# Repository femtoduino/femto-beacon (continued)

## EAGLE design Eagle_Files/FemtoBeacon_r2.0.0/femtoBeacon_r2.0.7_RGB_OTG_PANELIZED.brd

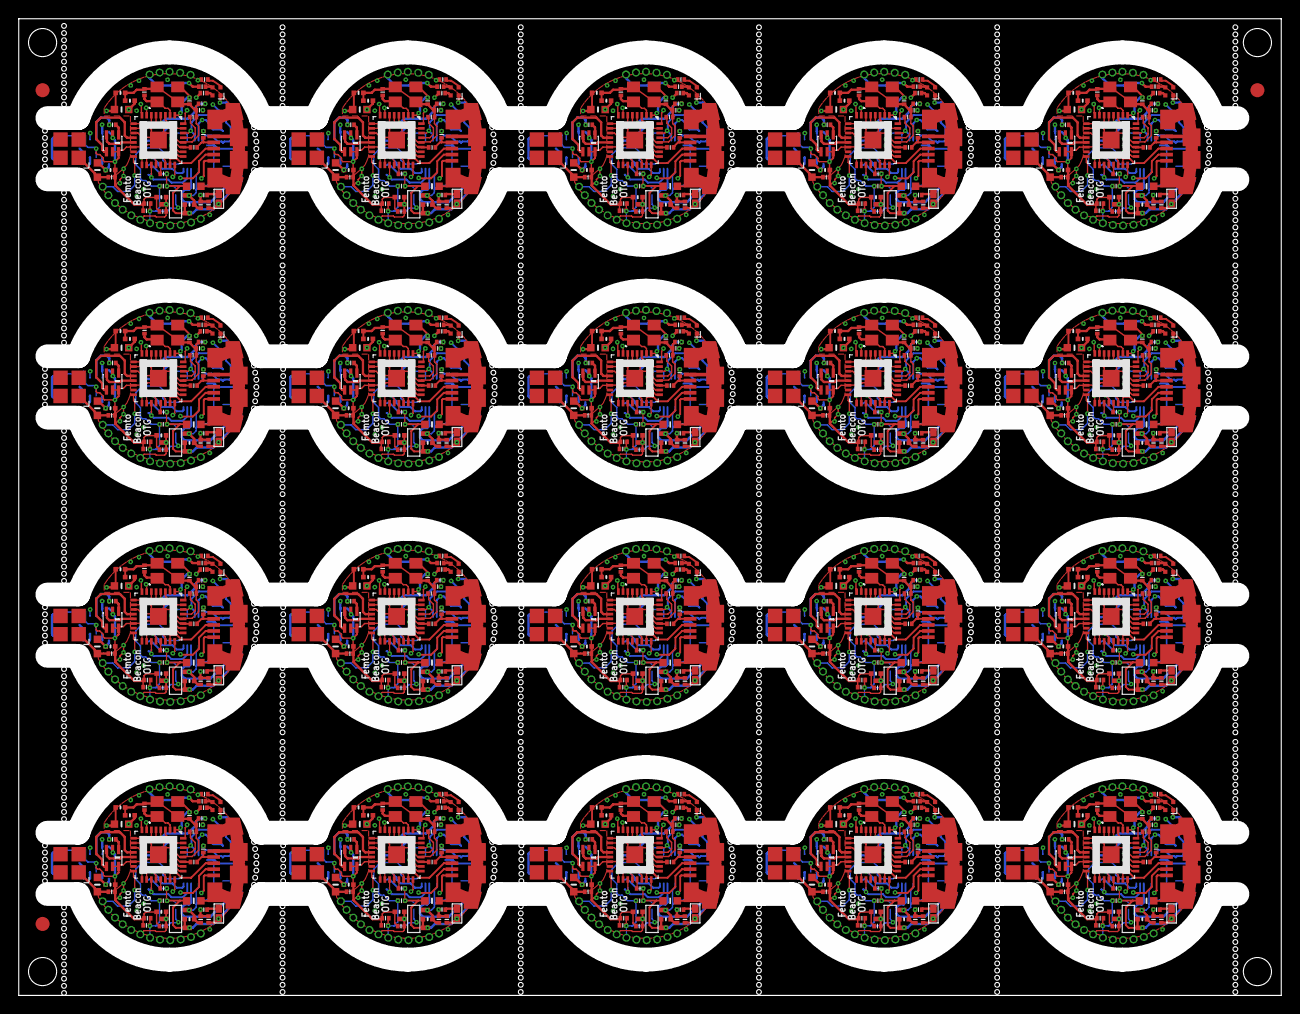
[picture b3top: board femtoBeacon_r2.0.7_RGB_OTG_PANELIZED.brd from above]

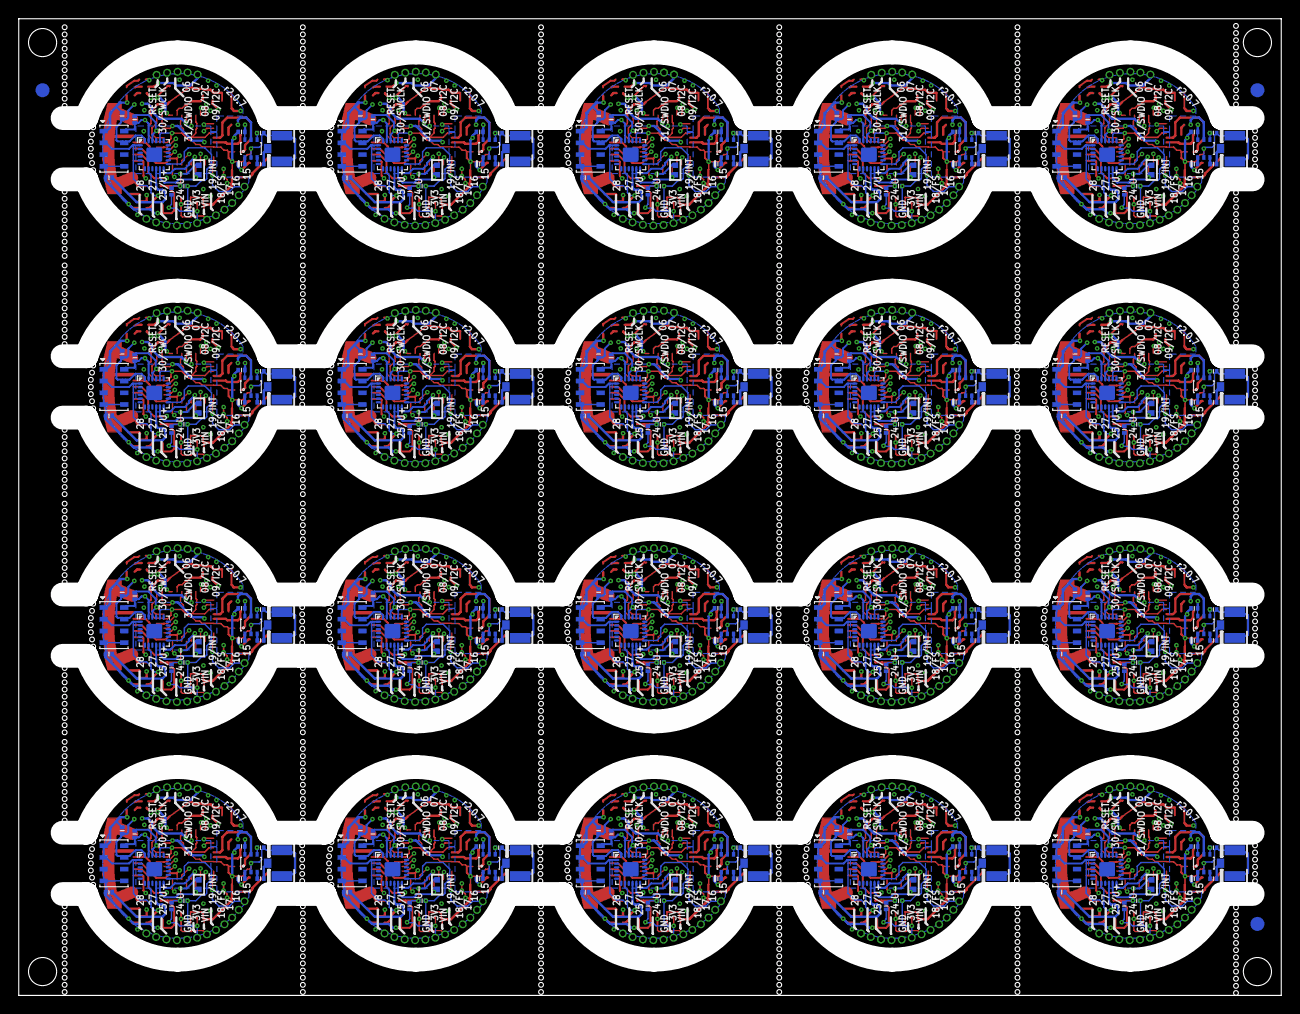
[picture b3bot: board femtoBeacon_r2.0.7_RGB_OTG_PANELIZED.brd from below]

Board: 4 copper layers, 134.6 x 104.1 mm, 1346 parts (283 on the bottom side), 820 nets.

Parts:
ANT_SMD, ANT_SMD1, ANT_SMD2, ANT_SMD3, ANT_SMD4, ANT_SMD5, ANT_SMD6, ANT_SMD7, ANT_SMD8, ANT_SMD9, ANT_SMD10, ANT_SMD11, ANT_SMD12, ANT_SMD13, ANT_SMD14, ANT_SMD15, ANT_SMD16, ANT_SMD17, ANT_SMD18, ANT_SMD19: 0479480001
ASWITCH, ASWITCH1, ASWITCH2, ASWITCH3, ASWITCH4, ASWITCH5, ASWITCH6, ASWITCH7, ASWITCH8, ASWITCH9, ASWITCH10, ASWITCH11, ASWITCH12, ASWITCH13, ASWITCH14, ASWITCH15, ASWITCH16, ASWITCH17, ASWITCH18, ASWITCH19: AS222-92LF
BALUN, BALUN1, BALUN2, BALUN3, BALUN4, BALUN5, BALUN6, BALUN7, BALUN8, BALUN9, BALUN10, BALUN11, BALUN12, BALUN13, BALUN14, BALUN15, BALUN16, BALUN17, BALUN18, BALUN19: JOHANSON_2450BM15A0015E; 0805_BALUN
BARO, BARO1, BARO2, BARO3, BARO4, BARO5, BARO6, BARO7, BARO8, BARO9, BARO10, BARO11, BARO12, BARO13, BARO14, BARO15, BARO16, BARO17, BARO18, BARO19: MS5611-01BA03
BTN, BTN1, BTN2, BTN3, BTN4, BTN5, BTN6, BTN7, BTN8, BTN9, BTN10, BTN11, BTN12, BTN13, BTN14, BTN15, BTN16, BTN17, BTN18, BTN19: DNP; SPST_SMD
C1, C2, C3, C4, C8, C9, C10, C16, C17, C27, C28, C29, C30, C32, C33, C34, C35, C38, C42, C43, C51, C52, C56, C57, C58, C59, C60, C63, C67, C68, C76, C77, C81, C82, C83, C84, C85, C88, C92, C93, C101, C102, C106, C107, C108, C109, C110, C113, C117, C118, C126, C127, C131, C132, C133, C134, C135, C138, C142, C143, C151, C152, C156, C157, C158, C159, C160, C163, C167, C168, C176, C177, C181, C182, C183, C184, C185, C188, C192, C193, C201, C202, C206, C207, C208, C209, C210, C213, C217, C218, C226, C227, C231, C232, C233, C234, C235, C238, C242, C243, C251, C252, C256, C257, C258, C259, C260, C263, C267, C268, C276, C277, C281, C282, C283, C284, C285, C288, C292, C293, C301, C302, C306, C307, C308, C309, C310, C313, C317, C318, C326, C327, C331, C332, C333, C334, C335, C338, C342, C343, C351, C352, C356, C357, C358, C359, C360, C363, C367, C368, C376, C377, C381, C382, C383, C384, C385, C388, C392, C393, C401, C402, C406, C407, C408, C409, C410, C413, C417, C418, C426, C427, C431, C432, C433, C434, C435, C438, C442, C443, C451, C452, C456, C457, C458, C459, C460, C463, C467, C468, C476, C477, C481, C482, C483, C484, C485, C488, C492, C493: 0.1uF; PART
C5, C6, C24, C25, C53, C54, C78, C79, C103, C104, C128, C129, C153, C154, C178, C179, C203, C204, C228, C229, C253, C254, C278, C279, C303, C304, C328, C329, C353, C354, C378, C379, C403, C404, C428, C429, C453, C454, C478, C479: 2.2uF; _0402MP
C7, C26, C55, C80, C105, C130, C155, C180, C205, C230, C255, C280, C305, C330, C355, C380, C405, C430, C455, C480: 0.47uF; PART
C11, C45, C70, C95, C120, C145, C170, C195, C220, C245, C270, C295, C320, C345, C370, C395, C420, C445, C470, C495: 1.2pF; _0402MP
C12, C18, C19, C20, C23, C46, C47, C48, C49, C50, C71, C72, C73, C74, C75, C96, C97, C98, C99, C100, C121, C122, C123, C124, C125, C146, C147, C148, C149, C150, C171, C172, C173, C174, C175, C196, C197, C198, C199, C200, C221, C222, C223, C224, C225, C246, C247, C248, C249, C250, C271, C272, C273, C274, C275, C296, C297, C298, C299, C300, C321, C322, C323, C324, C325, C346, C347, C348, C349, C350, C371, C372, C373, C374, C375, C396, C397, C398, C399, C400, C421, C422, C423, C424, C425, C446, C447, C448, C449, C450, C471, C472, C473, C474, C475, C496, C497, C498, C499, C500: 22pF; PART
C13, C44, C69, C94, C119, C144, C169, C194, C219, C244, C269, C294, C319, C344, C369, C394, C419, C444, C469, C494: DNP; PART
C14, C15, C39, C40, C64, C65, C89, C90, C114, C115, C139, C140, C164, C165, C189, C190, C214, C215, C239, C240, C264, C265, C289, C290, C314, C315, C339, C340, C364, C365, C389, C390, C414, C415, C439, C440, C464, C465, C489, C490: 9pF; PART
C21, C22, C36, C37, C61, C62, C86, C87, C111, C112, C136, C137, C161, C162, C186, C187, C211, C212, C236, C237, C261, C262, C286, C287, C311, C312, C336, C337, C361, C362, C386, C387, C411, C412, C436, C437, C461, C462, C486, C487: 10uF; _0402MP
C31, C41, C66, C91, C116, C141, C166, C191, C216, C241, C266, C291, C316, C341, C366, C391, C416, C441, C466, C491: 10nF; PART
FB1, FB2, FB3, FB4, FB5, FB6, FB7, FB8, FB9, FB10, FB11, FB12, FB13, FB14, FB15, FB16, FB17, FB18, FB19, FB20: Ferrite; _0603MP
FID1, FID2, FID3, FID4, FID5, FID6: FIDUCIAL; FIDUCIAL_1MM
IC, IC1, IC2, IC3, IC4, IC5, IC6, IC7, IC8, IC9, IC10, IC11, IC12, IC13, IC14, IC15, IC16, IC17, IC18, IC19: ATSAMR21E18A-MUT; QFN32
IMU, IMU1, IMU2, IMU3, IMU4, IMU5, IMU6, IMU7, IMU8, IMU9, IMU10, IMU11, IMU12, IMU13, IMU14, IMU15, IMU16, IMU17, IMU18, IMU19: MPU-9250; QFN_3X3MM
L1, L3, L5, L8, L10, L12, L14, L16, L18, L20, L22, L24, L26, L28, L30, L32, L34, L36, L38, L40: 1.8nH; _0603MP
L2, L4, L6, L7, L9, L11, L13, L15, L17, L19, L21, L23, L25, L27, L29, L31, L33, L35, L37, L39: 10uH; _0603MP
LDO_VREG, LDO_VREG1, LDO_VREG2, LDO_VREG3, LDO_VREG4, LDO_VREG5, LDO_VREG6, LDO_VREG7, LDO_VREG8, LDO_VREG9, LDO_VREG10, LDO_VREG11, LDO_VREG12, LDO_VREG13, LDO_VREG14, LDO_VREG15, LDO_VREG16, LDO_VREG17, LDO_VREG18, LDO_VREG19: MCP1700T-3302E/TT
R1, R4, R5, R6, R7, R11, R16, R17, R18, R19, R21, R26, R27, R28, R29, R31, R36, R37, R38, R39, R41, R46, R47, R48, R49, R51, R56, R57, R58, R59, R61, R66, R67, R68, R69, R71, R76, R77, R78, R79, R81, R86, R87, R88, R89, R91, R96, R97, R98, R99, R101, R106, R107, R108, R109, R111, R116, R117, R118, R119, R121, R126, R127, R128, R129, R131, R136, R137, R138, R139, R141, R146, R147, R148, R149, R151, R156, R157, R158, R159, R161, R166, R167, R168, R169, R171, R176, R177, R178, R179, R181, R186, R187, R188, R189, R191, R196, R197, R198, R199: 330; PART
R2, R12, R22, R32, R42, R52, R62, R72, R82, R92, R102, R112, R122, R132, R142, R152, R162, R172, R182, R192: 10K; PART
R3, R15, R25, R35, R45, R55, R65, R75, R85, R95, R105, R115, R125, R135, R145, R155, R165, R175, R185, R195: 330; _0402
R8, R9, R13, R14, R23, R24, R33, R34, R43, R44, R53, R54, R63, R64, R73, R74, R83, R84, R93, R94, R103, R104, R113, R114, R123, R124, R133, R134, R143, R144, R153, R154, R163, R164, R173, R174, R183, R184, R193, R194: 2.2K; PART
R10, R20, R30, R40, R50, R60, R70, R80, R90, R100, R110, R120, R130, R140, R150, R160, R170, R180, R190, R200: 100K; PART
RGBLED, RGBLED1, RGBLED2, RGBLED3, RGBLED4, RGBLED5, RGBLED6, RGBLED7, RGBLED8, RGBLED9, RGBLED10, RGBLED11, RGBLED12, RGBLED13, RGBLED14, RGBLED15, RGBLED16, RGBLED17, RGBLED18, RGBLED19: LRTB_R48G
U$1, U$2, U$3, U$4, U$5, U$6, U$7, U$8, U$9, U$10, U$11, U$12, U$13, U$14, U$15, U$16, U$17, U$18, U$19, U$20, U$21, U$22, U$23, U$24, U$25, U$26, U$27, U$28, U$29, U$30, U$31, U$32, U$33, U$34, U$35, U$36, U$37, U$38, U$39, U$40, U$41, U$42, U$43, U$44, U$45, U$46, U$47, U$48, U$49, U$50, U$51, U$52, U$53, U$54, U$55, U$56, U$57, U$58, U$59, U$60, U$61, U$62, U$63, U$64, U$65, U$66, U$67, U$68, U$69, U$70, U$71, U$72, U$73, U$74, U$75, U$76, U$77, U$78, U$79, U$80, U$81, U$82, U$83, U$84, U$85, U$86, U$87, U$88, U$89, U$90, U$91, U$92, U$93, U$94, U$95, U$96, U$97, U$98, U$99, U$100, U$101, U$102, U$103, U$104, U$105, U$106, U$107, U$108, U$109, U$110, U$111, U$112, U$113, U$114, U$115, U$116, U$117, U$118, U$119, U$120, U$121, U$122, U$123, U$124, U$125, U$126, U$127, U$128, U$129, U$130, U$131, U$132, U$133, U$134, U$135, U$136, U$137, U$138, U$139, U$140, U$141, U$142, U$143, U$144, U$145, U$146, U$147, U$148, U$149, U$150, U$151, U$152, U$153, U$154, U$155, U$156, U$157, U$158, U$159, U$160, U$161, U$162, U$163, U$164, U$165, U$166, U$167, U$168, U$169, U$170, U$171, U$172, U$173, U$174, U$175, U$176, U$177, U$178, U$179, U$180, U$181, U$182, U$183, U$184, U$185, U$186, U$187, U$188, U$189, U$190, U$191, U$192, U$193, U$194, U$195, U$196, U$197, U$198, U$199, U$200, U$201, U$202, U$203, U$204, U$205, U$206, U$207, U$208, U$209, U$210, U$211, U$212, U$213, U$214, U$215, U$216, U$217, U$218, U$219, U$220, U$221, U$222, U$223, U$224, U$225, U$226, U$227, U$228, U$229, U$230, U$231, U$232, U$233, U$234, U$235, U$236, U$237, U$238, U$239, U$240, U$241, U$242, U$243, U$244, U$245, U$246, U$247, U$248, U$249, U$250, U$251, U$252, U$253, U$254, U$255, U$256, U$257, U$258, U$259, U$260, U$261, U$262, U$263, U$264, U$265, U$266, U$267, U$268, U$269, U$270, U$271, U$272, U$273, U$274, U$275, U$276, U$277, U$278, U$279, U$280, U$281, U$282, U$283, U$284, U$285, U$286, U$287, U$288, U$289, U$290, U$291, U$292, U$293, U$294, U$295, U$296, U$297, U$298, U$299, U$300, U$301, U$302, U$303, U$304, U$305, U$306, U$307, U$308, U$309, U$310, U$311, U$312, U$313, U$314, U$315, U$316, U$317, U$318, U$319, U$320, U$321, U$322, U$323, U$324, U$325, U$326, U$327, U$328, U$329, U$330, U$331, U$332, U$333, U$334, U$335, U$336, U$337, U$338, U$339, U$340: 1X1_ROUND
UFLANT, UFLANT1, UFLANT2, UFLANT3, UFLANT4, UFLANT5, UFLANT6, UFLANT7, UFLANT8, UFLANT9, UFLANT10, UFLANT11, UFLANT12, UFLANT13, UFLANT14, UFLANT15, UFLANT16, UFLANT17, UFLANT18, UFLANT19: uFL; U.FL
USB, USB1, USB2, USB3, USB4, USB5, USB6, USB7, USB8, USB9, USB10, USB11, USB12, USB13, USB14, USB15, USB16, USB17, USB18, USB19: USB_MICROB; USB_MICROB_PACKAGE
XOSCRF, XOSCRF1, XOSCRF2, XOSCRF3, XOSCRF4, XOSCRF5, XOSCRF6, XOSCRF7, XOSCRF8, XOSCRF9, XOSCRF10, XOSCRF11, XOSCRF12, XOSCRF13, XOSCRF14, XOSCRF15, XOSCRF16, XOSCRF17, XOSCRF18, XOSCRF19: 16MHz; TSX-3225

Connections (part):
3.3V: BARO.1, BARO.2, C5.1, C10.1, C16.1, C21.2, C29.1, C30.2, C31.2, IC.24, IC.30, IMU.P$1, IMU.P$8, IMU.P$13, IMU.P$22, L6.1, LDO_VREG.VOUT, R2.2, R8.2, R9.2, R10.2, RGBLED.1, U$5.P$1
3.3V1: BARO1.1, BARO1.2, C24.1, C27.1, C34.1, C36.2, C38.1, C41.2, C42.2, IC1.24, IC1.30, IMU1.P$1, IMU1.P$8, IMU1.P$13, IMU1.P$22, L2.1, LDO_VREG1.VOUT, R12.2, R13.2, R14.2, R20.2, RGBLED1.1, U$6.P$1
3.3V2: BARO2.1, BARO2.2, C53.1, C56.1, C59.1, C61.2, C63.1, C66.2, C67.2, IC2.24, IC2.30, IMU2.P$1, IMU2.P$8, IMU2.P$13, IMU2.P$22, L4.1, LDO_VREG2.VOUT, R22.2, R23.2, R24.2, R30.2, RGBLED2.1, U$26.P$1
3.3V3: BARO3.1, BARO3.2, C78.1, C81.1, C84.1, C86.2, C88.1, C91.2, C92.2, IC3.24, IC3.30, IMU3.P$1, IMU3.P$8, IMU3.P$13, IMU3.P$22, L7.1, LDO_VREG3.VOUT, R32.2, R33.2, R34.2, R40.2, RGBLED3.1, U$53.P$1
3.3V4: BARO4.1, BARO4.2, C103.1, C106.1, C109.1, C111.2, C113.1, C116.2, C117.2, IC4.24, IC4.30, IMU4.P$1, IMU4.P$8, IMU4.P$13, IMU4.P$22, L9.1, LDO_VREG4.VOUT, R42.2, R43.2, R44.2, R50.2, RGBLED4.1, U$71.P$1
3.3V5: BARO5.1, BARO5.2, C128.1, C131.1, C134.1, C136.2, C138.1, C141.2, C142.2, IC5.24, IC5.30, IMU5.P$1, IMU5.P$8, IMU5.P$13, IMU5.P$22, L11.1, LDO_VREG5.VOUT, R52.2, R53.2, R54.2, R60.2, RGBLED5.1, U$88.P$1
3.3V6: BARO6.1, BARO6.2, C153.1, C156.1, C159.1, C161.2, C163.1, C166.2, C167.2, IC6.24, IC6.30, IMU6.P$1, IMU6.P$8, IMU6.P$13, IMU6.P$22, L13.1, LDO_VREG6.VOUT, R62.2, R63.2, R64.2, R70.2, RGBLED6.1, U$105.P$1
3.3V7: BARO7.1, BARO7.2, C178.1, C181.1, C184.1, C186.2, C188.1, C191.2, C192.2, IC7.24, IC7.30, IMU7.P$1, IMU7.P$8, IMU7.P$13, IMU7.P$22, L15.1, LDO_VREG7.VOUT, R72.2, R73.2, R74.2, R80.2, RGBLED7.1, U$122.P$1
3.3V8: BARO8.1, BARO8.2, C203.1, C206.1, C209.1, C211.2, C213.1, C216.2, C217.2, IC8.24, IC8.30, IMU8.P$1, IMU8.P$8, IMU8.P$13, IMU8.P$22, L17.1, LDO_VREG8.VOUT, R82.2, R83.2, R84.2, R90.2, RGBLED8.1, U$139.P$1
3.3V9: BARO9.1, BARO9.2, C228.1, C231.1, C234.1, C236.2, C238.1, C241.2, C242.2, IC9.24, IC9.30, IMU9.P$1, IMU9.P$8, IMU9.P$13, IMU9.P$22, L19.1, LDO_VREG9.VOUT, R92.2, R93.2, R94.2, R100.2, RGBLED9.1, U$156.P$1
3.3V10: BARO10.1, BARO10.2, C253.1, C256.1, C259.1, C261.2, C263.1, C266.2, C267.2, IC10.24, IC10.30, IMU10.P$1, IMU10.P$8, IMU10.P$13, IMU10.P$22, L21.1, LDO_VREG10.VOUT, R102.2, R103.2, R104.2, R110.2, RGBLED10.1, U$173.P$1
3.3V11: BARO11.1, BARO11.2, C278.1, C281.1, C284.1, C286.2, C288.1, C291.2, C292.2, IC11.24, IC11.30, IMU11.P$1, IMU11.P$8, IMU11.P$13, IMU11.P$22, L23.1, LDO_VREG11.VOUT, R112.2, R113.2, R114.2, R120.2, RGBLED11.1, U$190.P$1
3.3V12: BARO12.1, BARO12.2, C303.1, C306.1, C309.1, C311.2, C313.1, C316.2, C317.2, IC12.24, IC12.30, IMU12.P$1, IMU12.P$8, IMU12.P$13, IMU12.P$22, L25.1, LDO_VREG12.VOUT, R122.2, R123.2, R124.2, R130.2, RGBLED12.1, U$207.P$1
3.3V13: BARO13.1, BARO13.2, C328.1, C331.1, C334.1, C336.2, C338.1, C341.2, C342.2, IC13.24, IC13.30, IMU13.P$1, IMU13.P$8, IMU13.P$13, IMU13.P$22, L27.1, LDO_VREG13.VOUT, R132.2, R133.2, R134.2, R140.2, RGBLED13.1, U$224.P$1
3.3V14: BARO14.1, BARO14.2, C353.1, C356.1, C359.1, C361.2, C363.1, C366.2, C367.2, IC14.24, IC14.30, IMU14.P$1, IMU14.P$8, IMU14.P$13, IMU14.P$22, L29.1, LDO_VREG14.VOUT, R142.2, R143.2, R144.2, R150.2, RGBLED14.1, U$241.P$1
3.3V15: BARO15.1, BARO15.2, C378.1, C381.1, C384.1, C386.2, C388.1, C391.2, C392.2, IC15.24, IC15.30, IMU15.P$1, IMU15.P$8, IMU15.P$13, IMU15.P$22, L31.1, LDO_VREG15.VOUT, R152.2, R153.2, R154.2, R160.2, RGBLED15.1, U$258.P$1
3.3V16: BARO16.1, BARO16.2, C403.1, C406.1, C409.1, C411.2, C413.1, C416.2, C417.2, IC16.24, IC16.30, IMU16.P$1, IMU16.P$8, IMU16.P$13, IMU16.P$22, L33.1, LDO_VREG16.VOUT, R162.2, R163.2, R164.2, R170.2, RGBLED16.1, U$275.P$1
3.3V17: BARO17.1, BARO17.2, C428.1, C431.1, C434.1, C436.2, C438.1, C441.2, C442.2, IC17.24, IC17.30, IMU17.P$1, IMU17.P$8, IMU17.P$13, IMU17.P$22, L35.1, LDO_VREG17.VOUT, R172.2, R173.2, R174.2, R180.2, RGBLED17.1, U$292.P$1
3.3V18: BARO18.1, BARO18.2, C453.1, C456.1, C459.1, C461.2, C463.1, C466.2, C467.2, IC18.24, IC18.30, IMU18.P$1, IMU18.P$8, IMU18.P$13, IMU18.P$22, L37.1, LDO_VREG18.VOUT, R182.2, R183.2, R184.2, R190.2, RGBLED18.1, U$309.P$1
3.3V19: BARO19.1, BARO19.2, C478.1, C481.1, C484.1, C486.2, C488.1, C491.2, C492.2, IC19.24, IC19.30, IMU19.P$1, IMU19.P$8, IMU19.P$13, IMU19.P$22, L39.1, LDO_VREG19.VOUT, R192.2, R193.2, R194.2, R200.2, RGBLED19.1, U$326.P$1
ANT_LINE: ANT_SMD.ANT, C13.1, L1.2
ANT_LINE1: ANT_SMD1.ANT, C44.1, L3.2
ANT_LINE2: ANT_SMD2.ANT, C69.1, L5.2
ANT_LINE3: ANT_SMD3.ANT, C94.1, L8.2
ANT_LINE4: ANT_SMD4.ANT, C119.1, L10.2
ANT_LINE5: ANT_SMD5.ANT, C144.1, L12.2
ANT_LINE6: ANT_SMD6.ANT, C169.1, L14.2
ANT_LINE7: ANT_SMD7.ANT, C194.1, L16.2
ANT_LINE8: ANT_SMD8.ANT, C219.1, L18.2
ANT_LINE9: ANT_SMD9.ANT, C244.1, L20.2
ANT_LINE10: ANT_SMD10.ANT, C269.1, L22.2
ANT_LINE11: ANT_SMD11.ANT, C294.1, L24.2
ANT_LINE12: ANT_SMD12.ANT, C319.1, L26.2
ANT_LINE13: ANT_SMD13.ANT, C344.1, L28.2
ANT_LINE14: ANT_SMD14.ANT, C369.1, L30.2
ANT_LINE15: ANT_SMD15.ANT, C394.1, L32.2
ANT_LINE16: ANT_SMD16.ANT, C419.1, L34.2
ANT_LINE17: ANT_SMD17.ANT, C444.1, L36.2
ANT_LINE18: ANT_SMD18.ANT, C469.1, L38.2
ANT_LINE19: ANT_SMD19.ANT, C494.1, L40.2
ANT_OUT: BALUN.1, C12.1
ANT_OUT1: BALUN1.1, C46.1
ANT_OUT2: BALUN2.1, C71.1
ANT_OUT3: BALUN3.1, C96.1
ANT_OUT4: BALUN4.1, C121.1
ANT_OUT5: BALUN5.1, C146.1
ANT_OUT6: BALUN6.1, C171.1
ANT_OUT7: BALUN7.1, C196.1
ANT_OUT8: BALUN8.1, C221.1
ANT_OUT9: BALUN9.1, C246.1
ANT_OUT10: BALUN10.1, C271.1
ANT_OUT11: BALUN11.1, C296.1
ANT_OUT12: BALUN12.1, C321.1
ANT_OUT13: BALUN13.1, C346.1
ANT_OUT14: BALUN14.1, C371.1
ANT_OUT15: BALUN15.1, C396.1
ANT_OUT16: BALUN16.1, C421.1
ANT_OUT17: BALUN17.1, C446.1
ANT_OUT18: BALUN18.1, C471.1
ANT_OUT19: BALUN19.1, C496.1
ANT_SMD: C11.1, C23.2, L1.1
ANT_SMD1: C45.1, C50.2, L3.1
ANT_SMD2: C70.1, C75.2, L5.1
ANT_SMD3: C95.1, C100.2, L8.1
ANT_SMD4: C120.1, C125.2, L10.1
ANT_SMD5: C145.1, C150.2, L12.1
ANT_SMD6: C170.1, C175.2, L14.1
ANT_SMD7: C195.1, C200.2, L16.1
ANT_SMD8: C220.1, C225.2, L18.1
ANT_SMD9: C245.1, C250.2, L20.1
ANT_SMD10: C270.1, C275.2, L22.1
ANT_SMD11: C295.1, C300.2, L24.1
ANT_SMD12: C320.1, C325.2, L26.1
ANT_SMD13: C345.1, C350.2, L28.1
ANT_SMD14: C370.1, C375.2, L30.1
ANT_SMD15: C395.1, C400.2, L32.1
ANT_SMD16: C420.1, C425.2, L34.1
ANT_SMD17: C445.1, C450.2, L36.1
ANT_SMD18: C470.1, C475.2, L38.1
ANT_SMD19: C495.1, C500.2, L40.1
ANT_UFL: C20.1, UFLANT.3
ANT_UFL1: C49.1, UFLANT1.3
ANT_UFL2: C74.1, UFLANT2.3
ANT_UFL3: C99.1, UFLANT3.3
ANT_UFL4: C124.1, UFLANT4.3
ANT_UFL5: C149.1, UFLANT5.3
ANT_UFL6: C174.1, UFLANT6.3
ANT_UFL7: C199.1, UFLANT7.3
ANT_UFL8: C224.1, UFLANT8.3
ANT_UFL9: C249.1, UFLANT9.3
ANT_UFL10: C274.1, UFLANT10.3
ANT_UFL11: C299.1, UFLANT11.3
ANT_UFL12: C324.1, UFLANT12.3
ANT_UFL13: C349.1, UFLANT13.3
ANT_UFL14: C374.1, UFLANT14.3
ANT_UFL15: C399.1, UFLANT15.3
ANT_UFL16: C424.1, UFLANT16.3
ANT_UFL17: C449.1, UFLANT17.3
ANT_UFL18: C474.1, UFLANT18.3
ANT_UFL19: C499.1, UFLANT19.3
AVDD: C17.1, IC.5
AVDD1: C35.1, IC1.5
AVDD2: C60.1, IC2.5
AVDD3: C85.1, IC3.5
AVDD4: C110.1, IC4.5
AVDD5: C135.1, IC5.5
AVDD6: C160.1, IC6.5
AVDD7: C185.1, IC7.5
AVDD8: C210.1, IC8.5
AVDD9: C235.1, IC9.5
AVDD10: C260.1, IC10.5
AVDD11: C285.1, IC11.5
AVDD12: C310.1, IC12.5
AVDD13: C335.1, IC13.5
AVDD14: C360.1, IC14.5
AVDD15: C385.1, IC15.5
AVDD16: C410.1, IC16.5
AVDD17: C435.1, IC17.5
AVDD18: C460.1, IC18.5
AVDD19: C485.1, IC19.5
DVDD: C2.1, IC.21
DVDD1: C4.1, IC1.21
DVDD2: C52.1, IC2.21
DVDD3: C77.1, IC3.21
DVDD4: C102.1, IC4.21
DVDD5: C127.1, IC5.21
DVDD6: C152.1, IC6.21
DVDD7: C177.1, IC7.21
DVDD8: C202.1, IC8.21
DVDD9: C227.1, IC9.21
DVDD10: C252.1, IC10.21
DVDD11: C277.1, IC11.21
DVDD12: C302.1, IC12.21
DVDD13: C327.1, IC13.21
DVDD14: C352.1, IC14.21
DVDD15: C377.1, IC15.21
DVDD16: C402.1, IC16.21
DVDD17: C427.1, IC17.21
DVDD18: C452.1, IC18.21
DVDD19: C477.1, IC19.21
GND: ASWITCH.PIN2, BALUN.2, BALUN.5, BALUN.6, BARO.3, BARO.4, BARO.5, BTN.2, C1.2, C2.2, C5.2, C6.2, C7.2, C8.2, C9.2, C10.2, C11.2, C13.2, C14.1, C15.2, C16.2, C17.2, C18.1, C19.2, C21.1, C22.1, C29.2, C30.1, C31.1, C32.2, FB1.2, IC.3, IC.6, IC.11, IC.14, IC.28, IC.33, IMU.P$20, LDO_VREG.GND, R3.1, U$2.P$1, UFLANT.1, UFLANT.2, XOSCRF.2, XOSCRF.4
GND1: ASWITCH1.PIN2, BALUN1.2, BALUN1.5, BALUN1.6, BARO1.3, BARO1.4, BARO1.5, BTN1.2, C3.2, C4.2, C24.2, C25.2, C26.2, C27.2, C28.2, C33.2, C34.2, C35.2, C36.1, C37.1, C38.2, C39.1, C40.2, C41.1, C42.1, C43.2, C44.2, C45.2, C47.1, C48.2, FB2.2, IC1.3, IC1.6, IC1.11, IC1.14, IC1.28, IC1.33, IMU1.P$20, LDO_VREG1.GND, R15.1, U$4.P$1, UFLANT1.1, UFLANT1.2, XOSCRF1.2, XOSCRF1.4
GND2: ASWITCH2.PIN2, BALUN2.2, BALUN2.5, BALUN2.6, BARO2.3, BARO2.4, BARO2.5, BTN2.2, C51.2, C52.2, C53.2, C54.2, C55.2, C56.2, C57.2, C58.2, C59.2, C60.2, C61.1, C62.1, C63.2, C64.1, C65.2, C66.1, C67.1, C68.2, C69.2, C70.2, C72.1, C73.2, FB3.2, IC2.3, IC2.6, IC2.11, IC2.14, IC2.28, IC2.33, IMU2.P$20, LDO_VREG2.GND, R25.1, U$25.P$1, UFLANT2.1, UFLANT2.2, XOSCRF2.2, XOSCRF2.4
GND3: ASWITCH3.PIN2, BALUN3.2, BALUN3.5, BALUN3.6, BARO3.3, BARO3.4, BARO3.5, BTN3.2, C76.2, C77.2, C78.2, C79.2, C80.2, C81.2, C82.2, C83.2, C84.2, C85.2, C86.1, C87.1, C88.2, C89.1, C90.2, C91.1, C92.1, C93.2, C94.2, C95.2, C97.1, C98.2, FB4.2, IC3.3, IC3.6, IC3.11, IC3.14, IC3.28, IC3.33, IMU3.P$20, LDO_VREG3.GND, R35.1, U$52.P$1, UFLANT3.1, UFLANT3.2, XOSCRF3.2, XOSCRF3.4
GND4: ASWITCH4.PIN2, BALUN4.2, BALUN4.5, BALUN4.6, BARO4.3, BARO4.4, BARO4.5, BTN4.2, C101.2, C102.2, C103.2, C104.2, C105.2, C106.2, C107.2, C108.2, C109.2, C110.2, C111.1, C112.1, C113.2, C114.1, C115.2, C116.1, C117.1, C118.2, C119.2, C120.2, C122.1, C123.2, FB5.2, IC4.3, IC4.6, IC4.11, IC4.14, IC4.28, IC4.33, IMU4.P$20, LDO_VREG4.GND, R45.1, U$70.P$1, UFLANT4.1, UFLANT4.2, XOSCRF4.2, XOSCRF4.4
GND5: ASWITCH5.PIN2, BALUN5.2, BALUN5.5, BALUN5.6, BARO5.3, BARO5.4, BARO5.5, BTN5.2, C126.2, C127.2, C128.2, C129.2, C130.2, C131.2, C132.2, C133.2, C134.2, C135.2, C136.1, C137.1, C138.2, C139.1, C140.2, C141.1, C142.1, C143.2, C144.2, C145.2, C147.1, C148.2, FB6.2, IC5.3, IC5.6, IC5.11, IC5.14, IC5.28, IC5.33, IMU5.P$20, LDO_VREG5.GND, R55.1, U$87.P$1, UFLANT5.1, UFLANT5.2, XOSCRF5.2, XOSCRF5.4
GND6: ASWITCH6.PIN2, BALUN6.2, BALUN6.5, BALUN6.6, BARO6.3, BARO6.4, BARO6.5, BTN6.2, C151.2, C152.2, C153.2, C154.2, C155.2, C156.2, C157.2, C158.2, C159.2, C160.2, C161.1, C162.1, C163.2, C164.1, C165.2, C166.1, C167.1, C168.2, C169.2, C170.2, C172.1, C173.2, FB7.2, IC6.3, IC6.6, IC6.11, IC6.14, IC6.28, IC6.33, IMU6.P$20, LDO_VREG6.GND, R65.1, U$104.P$1, UFLANT6.1, UFLANT6.2, XOSCRF6.2, XOSCRF6.4
GND7: ASWITCH7.PIN2, BALUN7.2, BALUN7.5, BALUN7.6, BARO7.3, BARO7.4, BARO7.5, BTN7.2, C176.2, C177.2, C178.2, C179.2, C180.2, C181.2, C182.2, C183.2, C184.2, C185.2, C186.1, C187.1, C188.2, C189.1, C190.2, C191.1, C192.1, C193.2, C194.2, C195.2, C197.1, C198.2, FB8.2, IC7.3, IC7.6, IC7.11, IC7.14, IC7.28, IC7.33, IMU7.P$20, LDO_VREG7.GND, R75.1, U$121.P$1, UFLANT7.1, UFLANT7.2, XOSCRF7.2, XOSCRF7.4
GND8: ASWITCH8.PIN2, BALUN8.2, BALUN8.5, BALUN8.6, BARO8.3, BARO8.4, BARO8.5, BTN8.2, C201.2, C202.2, C203.2, C204.2, C205.2, C206.2, C207.2, C208.2, C209.2, C210.2, C211.1, C212.1, C213.2, C214.1, C215.2, C216.1, C217.1, C218.2, C219.2, C220.2, C222.1, C223.2, FB9.2, IC8.3, IC8.6, IC8.11, IC8.14, IC8.28, IC8.33, IMU8.P$20, LDO_VREG8.GND, R85.1, U$138.P$1, UFLANT8.1, UFLANT8.2, XOSCRF8.2, XOSCRF8.4
GND9: ASWITCH9.PIN2, BALUN9.2, BALUN9.5, BALUN9.6, BARO9.3, BARO9.4, BARO9.5, BTN9.2, C226.2, C227.2, C228.2, C229.2, C230.2, C231.2, C232.2, C233.2, C234.2, C235.2, C236.1, C237.1, C238.2, C239.1, C240.2, C241.1, C242.1, C243.2, C244.2, C245.2, C247.1, C248.2, FB10.2, IC9.3, IC9.6, IC9.11, IC9.14, IC9.28, IC9.33, IMU9.P$20, LDO_VREG9.GND, R95.1, U$155.P$1, UFLANT9.1, UFLANT9.2, XOSCRF9.2, XOSCRF9.4
GND10: ASWITCH10.PIN2, BALUN10.2, BALUN10.5, BALUN10.6, BARO10.3, BARO10.4, BARO10.5, BTN10.2, C251.2, C252.2, C253.2, C254.2, C255.2, C256.2, C257.2, C258.2, C259.2, C260.2, C261.1, C262.1, C263.2, C264.1, C265.2, C266.1, C267.1, C268.2, C269.2, C270.2, C272.1, C273.2, FB11.2, IC10.3, IC10.6, IC10.11, IC10.14, IC10.28, IC10.33, IMU10.P$20, LDO_VREG10.GND, R105.1, U$172.P$1, UFLANT10.1, UFLANT10.2, XOSCRF10.2, XOSCRF10.4
GND11: ASWITCH11.PIN2, BALUN11.2, BALUN11.5, BALUN11.6, BARO11.3, BARO11.4, BARO11.5, BTN11.2, C276.2, C277.2, C278.2, C279.2, C280.2, C281.2, C282.2, C283.2, C284.2, C285.2, C286.1, C287.1, C288.2, C289.1, C290.2, C291.1, C292.1, C293.2, C294.2, C295.2, C297.1, C298.2, FB12.2, IC11.3, IC11.6, IC11.11, IC11.14, IC11.28, IC11.33, IMU11.P$20, LDO_VREG11.GND, R115.1, U$189.P$1, UFLANT11.1, UFLANT11.2, XOSCRF11.2, XOSCRF11.4
GND12: ASWITCH12.PIN2, BALUN12.2, BALUN12.5, BALUN12.6, BARO12.3, BARO12.4, BARO12.5, BTN12.2, C301.2, C302.2, C303.2, C304.2, C305.2, C306.2, C307.2, C308.2, C309.2, C310.2, C311.1, C312.1, C313.2, C314.1, C315.2, C316.1, C317.1, C318.2, C319.2, C320.2, C322.1, C323.2, FB13.2, IC12.3, IC12.6, IC12.11, IC12.14, IC12.28, IC12.33, IMU12.P$20, LDO_VREG12.GND, R125.1, U$206.P$1, UFLANT12.1, UFLANT12.2, XOSCRF12.2, XOSCRF12.4
GND13: ASWITCH13.PIN2, BALUN13.2, BALUN13.5, BALUN13.6, BARO13.3, BARO13.4, BARO13.5, BTN13.2, C326.2, C327.2, C328.2, C329.2, C330.2, C331.2, C332.2, C333.2, C334.2, C335.2, C336.1, C337.1, C338.2, C339.1, C340.2, C341.1, C342.1, C343.2, C344.2, C345.2, C347.1, C348.2, FB14.2, IC13.3, IC13.6, IC13.11, IC13.14, IC13.28, IC13.33, IMU13.P$20, LDO_VREG13.GND, R135.1, U$223.P$1, UFLANT13.1, UFLANT13.2, XOSCRF13.2, XOSCRF13.4
GND14: ASWITCH14.PIN2, BALUN14.2, BALUN14.5, BALUN14.6, BARO14.3, BARO14.4, BARO14.5, BTN14.2, C351.2, C352.2, C353.2, C354.2, C355.2, C356.2, C357.2, C358.2, C359.2, C360.2, C361.1, C362.1, C363.2, C364.1, C365.2, C366.1, C367.1, C368.2, C369.2, C370.2, C372.1, C373.2, FB15.2, IC14.3, IC14.6, IC14.11, IC14.14, IC14.28, IC14.33, IMU14.P$20, LDO_VREG14.GND, R145.1, U$240.P$1, UFLANT14.1, UFLANT14.2, XOSCRF14.2, XOSCRF14.4
GND15: ASWITCH15.PIN2, BALUN15.2, BALUN15.5, BALUN15.6, BARO15.3, BARO15.4, BARO15.5, BTN15.2, C376.2, C377.2, C378.2, C379.2, C380.2, C381.2, C382.2, C383.2, C384.2, C385.2, C386.1, C387.1, C388.2, C389.1, C390.2, C391.1, C392.1, C393.2, C394.2, C395.2, C397.1, C398.2, FB16.2, IC15.3, IC15.6, IC15.11, IC15.14, IC15.28, IC15.33, IMU15.P$20, LDO_VREG15.GND, R155.1, U$257.P$1, UFLANT15.1, UFLANT15.2, XOSCRF15.2, XOSCRF15.4
GND16: ASWITCH16.PIN2, BALUN16.2, BALUN16.5, BALUN16.6, BARO16.3, BARO16.4, BARO16.5, BTN16.2, C401.2, C402.2, C403.2, C404.2, C405.2, C406.2, C407.2, C408.2, C409.2, C410.2, C411.1, C412.1, C413.2, C414.1, C415.2, C416.1, C417.1, C418.2, C419.2, C420.2, C422.1, C423.2, FB17.2, IC16.3, IC16.6, IC16.11, IC16.14, IC16.28, IC16.33, IMU16.P$20, LDO_VREG16.GND, R165.1, U$274.P$1, UFLANT16.1, UFLANT16.2, XOSCRF16.2, XOSCRF16.4
GND17: ASWITCH17.PIN2, BALUN17.2, BALUN17.5, BALUN17.6, BARO17.3, BARO17.4, BARO17.5, BTN17.2, C426.2, C427.2, C428.2, C429.2, C430.2, C431.2, C432.2, C433.2, C434.2, C435.2, C436.1, C437.1, C438.2, C439.1, C440.2, C441.1, C442.1, C443.2, C444.2, C445.2, C447.1, C448.2, FB18.2, IC17.3, IC17.6, IC17.11, IC17.14, IC17.28, IC17.33, IMU17.P$20, LDO_VREG17.GND, R175.1, U$291.P$1, UFLANT17.1, UFLANT17.2, XOSCRF17.2, XOSCRF17.4
GND18: ASWITCH18.PIN2, BALUN18.2, BALUN18.5, BALUN18.6, BARO18.3, BARO18.4, BARO18.5, BTN18.2, C451.2, C452.2, C453.2, C454.2, C455.2, C456.2, C457.2, C458.2, C459.2, C460.2, C461.1, C462.1, C463.2, C464.1, C465.2, C466.1, C467.1, C468.2, C469.2, C470.2, C472.1, C473.2, FB19.2, IC18.3, IC18.6, IC18.11, IC18.14, IC18.28, IC18.33, IMU18.P$20, LDO_VREG18.GND, R185.1, U$308.P$1, UFLANT18.1, UFLANT18.2, XOSCRF18.2, XOSCRF18.4
GND19: ASWITCH19.PIN2, BALUN19.2, BALUN19.5, BALUN19.6, BARO19.3, BARO19.4, BARO19.5, BTN19.2, C476.2, C477.2, C478.2, C479.2, C480.2, C481.2, C482.2, C483.2, C484.2, C485.2, C486.1, C487.1, C488.2, C489.1, C490.2, C491.1, C492.1, C493.2, C494.2, C495.2, C497.1, C498.2, FB20.2, IC19.3, IC19.6, IC19.11, IC19.14, IC19.28, IC19.33, IMU19.P$20, LDO_VREG19.GND, R195.1, U$325.P$1, UFLANT19.1, UFLANT19.2, XOSCRF19.2, XOSCRF19.4
unnamed: R5.2, R10.1, USB.4
unnamed: BTN1.1, R11.1
unnamed: C43.1, IMU1.P$10
unnamed: C32.1, IMU.P$10
unnamed: FB1.1, USB.5, USB.6, USB.7, USB.8, USB.9, USB.10, USB.11
unnamed: FB2.1, USB1.5, USB1.6, USB1.7, USB1.8, USB1.9, USB1.10, USB1.11
unnamed: R16.2, RGBLED1.2
unnamed: R6.2, RGBLED.3
unnamed: R7.2, RGBLED.4
unnamed: R17.2, RGBLED1.3
unnamed: R18.2, RGBLED1.4
unnamed: R19.2, R20.1, USB1.4
unnamed: R4.2, RGBLED.2
unnamed: BTN2.1, R21.1
unnamed: C68.1, IMU2.P$10
unnamed: FB3.1, USB2.5, USB2.6, USB2.7, USB2.8, USB2.9, USB2.10, USB2.11
unnamed: R26.2, RGBLED2.2
unnamed: R27.2, RGBLED2.3
unnamed: R28.2, RGBLED2.4
unnamed: R29.2, R30.1, USB2.4
unnamed: BTN3.1, R31.1
unnamed: C93.1, IMU3.P$10
unnamed: FB4.1, USB3.5, USB3.6, USB3.7, USB3.8, USB3.9, USB3.10, USB3.11
unnamed: R36.2, RGBLED3.2
unnamed: R37.2, RGBLED3.3
unnamed: BTN.1, R1.1
unnamed: R38.2, RGBLED3.4
unnamed: R39.2, R40.1, USB3.4
unnamed: BTN4.1, R41.1
unnamed: C118.1, IMU4.P$10
unnamed: FB5.1, USB4.5, USB4.6, USB4.7, USB4.8, USB4.9, USB4.10, USB4.11
unnamed: R46.2, RGBLED4.2
unnamed: R47.2, RGBLED4.3
unnamed: R48.2, RGBLED4.4
unnamed: R49.2, R50.1, USB4.4
unnamed: BTN5.1, R51.1
unnamed: C143.1, IMU5.P$10
unnamed: FB6.1, USB5.5, USB5.6, USB5.7, USB5.8, USB5.9, USB5.10, USB5.11
unnamed: R56.2, RGBLED5.2
unnamed: R57.2, RGBLED5.3
unnamed: R58.2, RGBLED5.4
unnamed: R59.2, R60.1, USB5.4
unnamed: BTN6.1, R61.1
unnamed: C168.1, IMU6.P$10
unnamed: FB7.1, USB6.5, USB6.6, USB6.7, USB6.8, USB6.9, USB6.10, USB6.11
unnamed: R66.2, RGBLED6.2
unnamed: R67.2, RGBLED6.3
unnamed: R68.2, RGBLED6.4
unnamed: R69.2, R70.1, USB6.4
unnamed: BTN7.1, R71.1
unnamed: C193.1, IMU7.P$10
unnamed: FB8.1, USB7.5, USB7.6, USB7.7, USB7.8, USB7.9, USB7.10, USB7.11
unnamed: R76.2, RGBLED7.2
unnamed: R77.2, RGBLED7.3
unnamed: R78.2, RGBLED7.4
unnamed: R79.2, R80.1, USB7.4
unnamed: BTN8.1, R81.1
unnamed: C218.1, IMU8.P$10
unnamed: FB9.1, USB8.5, USB8.6, USB8.7, USB8.8, USB8.9, USB8.10, USB8.11
unnamed: R86.2, RGBLED8.2
unnamed: R87.2, RGBLED8.3
unnamed: R88.2, RGBLED8.4
unnamed: R89.2, R90.1, USB8.4
unnamed: BTN9.1, R91.1
unnamed: C243.1, IMU9.P$10
unnamed: FB10.1, USB9.5, USB9.6, USB9.7, USB9.8, USB9.9, USB9.10, USB9.11
unnamed: R96.2, RGBLED9.2
unnamed: R97.2, RGBLED9.3
unnamed: R98.2, RGBLED9.4
unnamed: R99.2, R100.1, USB9.4
unnamed: BTN10.1, R101.1
unnamed: C268.1, IMU10.P$10
unnamed: FB11.1, USB10.5, USB10.6, USB10.7, USB10.8, USB10.9, USB10.10, USB10.11
unnamed: R106.2, RGBLED10.2
unnamed: R107.2, RGBLED10.3
unnamed: R108.2, RGBLED10.4
unnamed: R109.2, R110.1, USB10.4
unnamed: BTN11.1, R111.1
unnamed: C293.1, IMU11.P$10
unnamed: FB12.1, USB11.5, USB11.6, USB11.7, USB11.8, USB11.9, USB11.10, USB11.11
unnamed: R116.2, RGBLED11.2
unnamed: R117.2, RGBLED11.3
unnamed: R118.2, RGBLED11.4
unnamed: R119.2, R120.1, USB11.4
unnamed: BTN12.1, R121.1
unnamed: C318.1, IMU12.P$10
unnamed: FB13.1, USB12.5, USB12.6, USB12.7, USB12.8, USB12.9, USB12.10, USB12.11
unnamed: R126.2, RGBLED12.2
unnamed: R127.2, RGBLED12.3
unnamed: R128.2, RGBLED12.4
unnamed: R129.2, R130.1, USB12.4
unnamed: BTN13.1, R131.1
unnamed: C343.1, IMU13.P$10
unnamed: FB14.1, USB13.5, USB13.6, USB13.7, USB13.8, USB13.9, USB13.10, USB13.11
unnamed: R136.2, RGBLED13.2
unnamed: R137.2, RGBLED13.3
unnamed: R138.2, RGBLED13.4
unnamed: R139.2, R140.1, USB13.4
unnamed: BTN14.1, R141.1
unnamed: C368.1, IMU14.P$10
unnamed: FB15.1, USB14.5, USB14.6, USB14.7, USB14.8, USB14.9, USB14.10, USB14.11
unnamed: R146.2, RGBLED14.2
unnamed: R147.2, RGBLED14.3
unnamed: R148.2, RGBLED14.4
unnamed: R149.2, R150.1, USB14.4
unnamed: BTN15.1, R151.1
unnamed: C393.1, IMU15.P$10
unnamed: FB16.1, USB15.5, USB15.6, USB15.7, USB15.8, USB15.9, USB15.10, USB15.11
unnamed: R156.2, RGBLED15.2
unnamed: R157.2, RGBLED15.3
unnamed: R158.2, RGBLED15.4
unnamed: R159.2, R160.1, USB15.4
unnamed: BTN16.1, R161.1
unnamed: C418.1, IMU16.P$10
unnamed: FB17.1, USB16.5, USB16.6, USB16.7, USB16.8, USB16.9, USB16.10, USB16.11
unnamed: R166.2, RGBLED16.2
unnamed: R167.2, RGBLED16.3
unnamed: R168.2, RGBLED16.4
unnamed: R169.2, R170.1, USB16.4
unnamed: BTN17.1, R171.1
unnamed: C443.1, IMU17.P$10
unnamed: FB18.1, USB17.5, USB17.6, USB17.7, USB17.8, USB17.9, USB17.10, USB17.11
unnamed: R176.2, RGBLED17.2
unnamed: R177.2, RGBLED17.3
unnamed: R178.2, RGBLED17.4
unnamed: R179.2, R180.1, USB17.4
unnamed: BTN18.1, R181.1
unnamed: C468.1, IMU18.P$10
unnamed: FB19.1, USB18.5, USB18.6, USB18.7, USB18.8, USB18.9, USB18.10, USB18.11
unnamed: R186.2, RGBLED18.2
unnamed: R187.2, RGBLED18.3
unnamed: R188.2, RGBLED18.4
unnamed: R189.2, R190.1, USB18.4
unnamed: BTN19.1, R191.1
unnamed: C493.1, IMU19.P$10
unnamed: FB20.1, USB19.5, USB19.6, USB19.7, USB19.8, USB19.9, USB19.10, USB19.11
unnamed: R196.2, RGBLED19.2
unnamed: R197.2, RGBLED19.3
unnamed: R198.2, RGBLED19.4
unnamed: R199.2, R200.1, USB19.4
PA1: IC1.27, R19.1, U$20.P$1
PA2: IC2.27, R29.1, U$42.P$1
PA3: IC3.27, R39.1, U$65.P$1
PA4: IC4.27, R49.1, U$82.P$1
PA5: IC5.27, R59.1, U$99.P$1
PA6: IC6.27, R69.1, U$116.P$1
PA06(R): IC.7, R4.1, U$54.P$1
PA06(R)1: IC1.7, R16.1, U$21.P$1
PA06(R)2: IC2.7, R26.1, U$44.P$1
PA06(R)3: IC3.7, R36.1, U$66.P$1
PA06(R)4: IC4.7, R46.1, U$83.P$1
PA06(R)5: IC5.7, R56.1, U$100.P$1
PA06(R)6: IC6.7, R66.1, U$117.P$1
PA06(R)7: IC7.7, R76.1, U$134.P$1
PA06(R)8: IC8.7, R86.1, U$151.P$1
PA06(R)9: IC9.7, R96.1, U$168.P$1
PA06(R)10: IC10.7, R106.1, U$185.P$1
PA06(R)11: IC11.7, R116.1, U$202.P$1
PA06(R)12: IC12.7, R126.1, U$219.P$1
PA06(R)13: IC13.7, R136.1, U$236.P$1
PA06(R)14: IC14.7, R146.1, U$253.P$1
PA06(R)15: IC15.7, R156.1, U$270.P$1
PA06(R)16: IC16.7, R166.1, U$287.P$1
PA06(R)17: IC17.7, R176.1, U$304.P$1
PA06(R)18: IC18.7, R186.1, U$321.P$1
PA06(R)19: IC19.7, R196.1, U$338.P$1
PA7: IC7.27, R79.1, U$133.P$1
PA07(G): IC.8, R6.1, U$43.P$1
PA07(G)1: IC1.8, R17.1, U$15.P$1
PA07(G)2: IC2.8, R27.1, U$32.P$1
PA07(G)3: IC3.8, R37.1, U$60.P$1
PA07(G)4: IC4.8, R47.1, U$77.P$1
PA07(G)5: IC5.8, R57.1, U$94.P$1
PA07(G)6: IC6.8, R67.1, U$111.P$1
PA07(G)7: IC7.8, R77.1, U$128.P$1
PA07(G)8: IC8.8, R87.1, U$145.P$1
PA07(G)9: IC9.8, R97.1, U$162.P$1
PA07(G)10: IC10.8, R107.1, U$179.P$1
PA07(G)11: IC11.8, R117.1, U$196.P$1
PA07(G)12: IC12.8, R127.1, U$213.P$1
PA07(G)13: IC13.8, R137.1, U$230.P$1
PA07(G)14: IC14.8, R147.1, U$247.P$1
PA07(G)15: IC15.8, R157.1, U$264.P$1
PA07(G)16: IC16.8, R167.1, U$281.P$1
PA07(G)17: IC17.8, R177.1, U$298.P$1
PA07(G)18: IC18.8, R187.1, U$315.P$1
PA07(G)19: IC19.8, R197.1, U$332.P$1
PA8: IC8.27, R89.1, U$150.P$1
PA08/I2C/SDA: ASWITCH.PIN6, C19.1, IC.9
PA08/I2C/SDA1: ASWITCH1.PIN6, C48.1, IC1.9
PA08/I2C/SDA2: ASWITCH2.PIN6, C73.1, IC2.9
PA08/I2C/SDA3: ASWITCH3.PIN6, C98.1, IC3.9
PA08/I2C/SDA4: ASWITCH4.PIN6, C123.1, IC4.9
PA08/I2C/SDA5: ASWITCH5.PIN6, C148.1, IC5.9
PA08/I2C/SDA6: ASWITCH6.PIN6, C173.1, IC6.9
PA08/I2C/SDA7: ASWITCH7.PIN6, C198.1, IC7.9
PA08/I2C/SDA8: ASWITCH8.PIN6, C223.1, IC8.9
PA08/I2C/SDA9: ASWITCH9.PIN6, C248.1, IC9.9
PA08/I2C/SDA10: ASWITCH10.PIN6, C273.1, IC10.9
PA08/I2C/SDA11: ASWITCH11.PIN6, C298.1, IC11.9
PA08/I2C/SDA12: ASWITCH12.PIN6, C323.1, IC12.9
PA08/I2C/SDA13: ASWITCH13.PIN6, C348.1, IC13.9
PA08/I2C/SDA14: ASWITCH14.PIN6, C373.1, IC14.9
PA08/I2C/SDA15: ASWITCH15.PIN6, C398.1, IC15.9
PA08/I2C/SDA16: ASWITCH16.PIN6, C423.1, IC16.9
PA08/I2C/SDA17: ASWITCH17.PIN6, C448.1, IC17.9
PA08/I2C/SDA18: ASWITCH18.PIN6, C473.1, IC18.9
PA08/I2C/SDA19: ASWITCH19.PIN6, C498.1, IC19.9
PA9: IC9.27, R99.1, U$167.P$1
PA09/I2C/SCL: ASWITCH.PIN4, C18.2, IC.10
PA09/I2C/SCL1: ASWITCH1.PIN4, C47.2, IC1.10
PA09/I2C/SCL2: ASWITCH2.PIN4, C72.2, IC2.10
PA09/I2C/SCL3: ASWITCH3.PIN4, C97.2, IC3.10
PA09/I2C/SCL4: ASWITCH4.PIN4, C122.2, IC4.10
PA09/I2C/SCL5: ASWITCH5.PIN4, C147.2, IC5.10
PA09/I2C/SCL6: ASWITCH6.PIN4, C172.2, IC6.10
PA09/I2C/SCL7: ASWITCH7.PIN4, C197.2, IC7.10
PA09/I2C/SCL8: ASWITCH8.PIN4, C222.2, IC8.10
PA09/I2C/SCL9: ASWITCH9.PIN4, C247.2, IC9.10
PA09/I2C/SCL10: ASWITCH10.PIN4, C272.2, IC10.10
PA09/I2C/SCL11: ASWITCH11.PIN4, C297.2, IC11.10
PA09/I2C/SCL12: ASWITCH12.PIN4, C322.2, IC12.10
PA09/I2C/SCL13: ASWITCH13.PIN4, C347.2, IC13.10
PA09/I2C/SCL14: ASWITCH14.PIN4, C372.2, IC14.10
PA09/I2C/SCL15: ASWITCH15.PIN4, C397.2, IC15.10
PA09/I2C/SCL16: ASWITCH16.PIN4, C422.2, IC16.10
PA09/I2C/SCL17: ASWITCH17.PIN4, C447.2, IC17.10
PA09/I2C/SCL18: ASWITCH18.PIN4, C472.2, IC18.10
PA09/I2C/SCL19: ASWITCH19.PIN4, C497.2, IC19.10
PA10: IC10.27, R109.1, U$184.P$1
PA11: IC11.27, R119.1, U$201.P$1
PA12: IC12.27, R129.1, U$218.P$1
PA13: IC13.27, R139.1, U$235.P$1
PA14: IC14.27, R149.1, U$252.P$1
PA15: IC15.27, R159.1, U$269.P$1
PA15/XOUT_MC/TX: IC.16, U$39.P$1
PA15/XOUT_MC/TX1: IC1.16, U$14.P$1
PA15/XOUT_MC/TX2: IC2.16, U$31.P$1
PA15/XOUT_MC/TX3: IC3.16, U$59.P$1
PA15/XOUT_MC/TX4: IC4.16, U$76.P$1
PA15/XOUT_MC/TX5: IC5.16, U$93.P$1
PA15/XOUT_MC/TX6: IC6.16, U$110.P$1
PA15/XOUT_MC/TX7: IC7.16, U$127.P$1
PA15/XOUT_MC/TX8: IC8.16, U$144.P$1
PA15/XOUT_MC/TX9: IC9.16, U$161.P$1
PA15/XOUT_MC/TX10: IC10.16, U$178.P$1
PA15/XOUT_MC/TX11: IC11.16, U$195.P$1
PA15/XOUT_MC/TX12: IC12.16, U$212.P$1
PA15/XOUT_MC/TX13: IC13.16, U$229.P$1
PA15/XOUT_MC/TX14: IC14.16, U$246.P$1
PA15/XOUT_MC/TX15: IC15.16, U$263.P$1
PA15/XOUT_MC/TX16: IC16.16, U$280.P$1
PA15/XOUT_MC/TX17: IC17.16, U$297.P$1
PA15/XOUT_MC/TX18: IC18.16, U$314.P$1
PA15/XOUT_MC/TX19: IC19.16, U$331.P$1
PA16: IC16.27, R169.1, U$286.P$1
PA16/I2C: BARO.7, IC.17, IMU.P$24, R8.1, U$38.P$1
PA16/I2C1: BARO1.7, IC1.17, IMU1.P$24, R13.1, U$13.P$1
PA16/I2C2: BARO2.7, IC2.17, IMU2.P$24, R23.1, U$30.P$1
PA16/I2C3: BARO3.7, IC3.17, IMU3.P$24, R33.1, U$58.P$1
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
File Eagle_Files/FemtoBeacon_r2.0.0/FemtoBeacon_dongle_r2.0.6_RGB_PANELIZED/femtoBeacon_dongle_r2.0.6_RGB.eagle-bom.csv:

Qty,Value,Device,Package,Parts,Description,MFR_ID
2,,FERRITE_0603MP,_0603MP,"FB1, FB2",Ferrite Bead,BLM18RK102SN1D
1,,USB_TYPEA,USB_A-SMT,CN1,USB - Type A Connectors,Keystone 931
7,0.1uF,CAPACITOR_0201,PART,"C1, C2, C8, C9, C10, C16, C17",,GRM033C80J104KE84D
1,0.47uF,CAPACITOR_0201,PART,C7,,C0603X5R0J474K030BC
1,479480001,479480001,479480001,U$6,,51T4020
1,1.2pF,CAP_CERAMIC_0402MP,_0402MP,C11,Ceramic Capacitors,GRM1555C1H1R2BA01D
1,1.8nH,INDUCTOR_0603MP,_0603MP,L1,Inductors,L-14C1N8SV4T
1,10K,RESISTOR_0201,PART,R2,,RC0402FR-0710KL
2,10uF,CAP_CERAMIC_0402MP,_0402MP,"C21, C22",Ceramic Capacitors,AMK105CBJ106MV-F
1,10uH,INDUCTOR_0603MP,_0603MP,L6,Inductors,LQM18FN100M00D
1,16MHz,TSX-3225,TSX-3225,XOSCRF,,TSX-3225 16.0000MF09Z-AC0
1,DNP,1X5_ROUND,1X5_ROUND,U$1,,
2,2.2uF,CAP_CERAMIC_0402MP,_0402MP,"C5, C6",Ceramic Capacitors,C1005X5R1A225K050BC
5,22pF,CAPACITOR_0201,PART,"C18, C19, C20, C23, C24",,GRM0335C1E220JA01D
4,330,RESISTOR_0201,PART,"R1, R4, R6, R7",,CRCW0201330RJNED
2,9pF,CAPACITOR_0201,PART,"C14, C15",,C0603C0G1E090B030BG
1,AS222-92LF,AS222-92LF,AS222-92LF,ASWITCH,,AS222-92LF
1,ATSAMR21E18A-MUT,ATSAMR21E18A-MUT,QFN32,U$76,This is the ATMEL SAMR21E QFN-32. ATSAMR21E18A,ATSAMR21E18A-MFT
1,DNP,CAPACITOR_0201,PART,C13,,
1,DNP,SPST_SMD,SPST_SMD,BTN,,
3,FIDUCIAL,FIDUCIAL,FIDUCIAL_1MM,"FID1, FID2, FID3","For use by pick and place machines to calibrate the vision/machine, 1mm",
1,JOHANSON_2450BM15A0015E,JOHANSON_2450BM15A0015E,0805_BALUN,U$12,,2450BM15A0015E
1,LRTB_R48G,LRTB_R48G,LRTB_R48G,RGBLED,,LRTB R48G
1,MCP1700T-3302E/TT,MCP1700T-3302E/TT,MCP1700T-3302E/TT,LDO_VREG,"Microchip LDO ""MCP1700"" in a 3-Pin SOT-23 package.",MCP1700T-3302E/TT
1,uFL,ANTENNA_U.FL,U.FL,UFLANT,U.FL Antenna Connector,734120110
